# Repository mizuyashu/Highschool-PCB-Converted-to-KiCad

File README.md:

# Highschool-PCB-Converted-to-KiCad
the pcb that I made in the stem club workshop that was ordered on jlcpbc for free from the onboard hackclub free pcb thing hackclub was doing for highschoolers converted from the easy eda files to KiCad

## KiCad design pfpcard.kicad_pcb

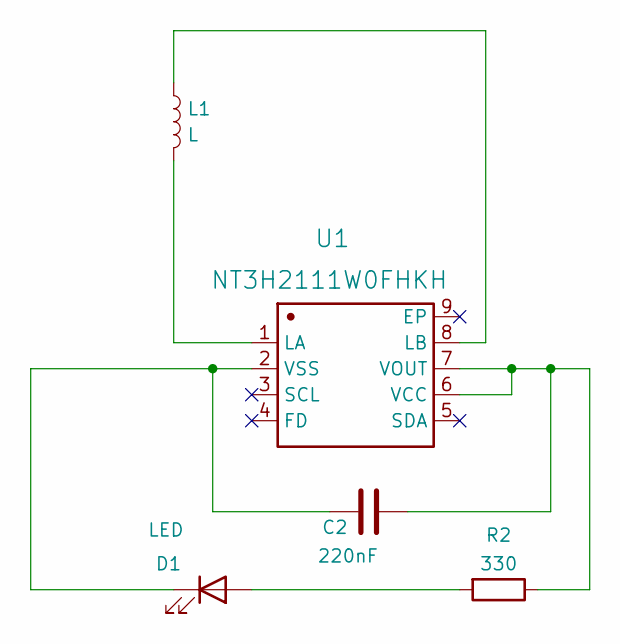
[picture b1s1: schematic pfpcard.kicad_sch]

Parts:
C2: 220nF; C_0603_1608Metric
D1: LED; LED_0805_2012Metric
L1: L; 25X48MM_NFC_ANTENNA
R2: 330; R_0603_1608Metric
U1: NT3H2111W0FHKH; XQFN-8_L1.6-W1.6-P0.50-BL; Manufacturer Part NT3H2111W0FHKH

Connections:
unnamed: D1.2 (A), R2.2
unnamed: C2.1, D1.1 (K), U1.2 (VSS)
unnamed: L1.2, U1.1 (LA)
unnamed: L1.1, U1.8 (LB)
unnamed: C2.2, R2.1, U1.6 (VCC), U1.7 (VOUT)

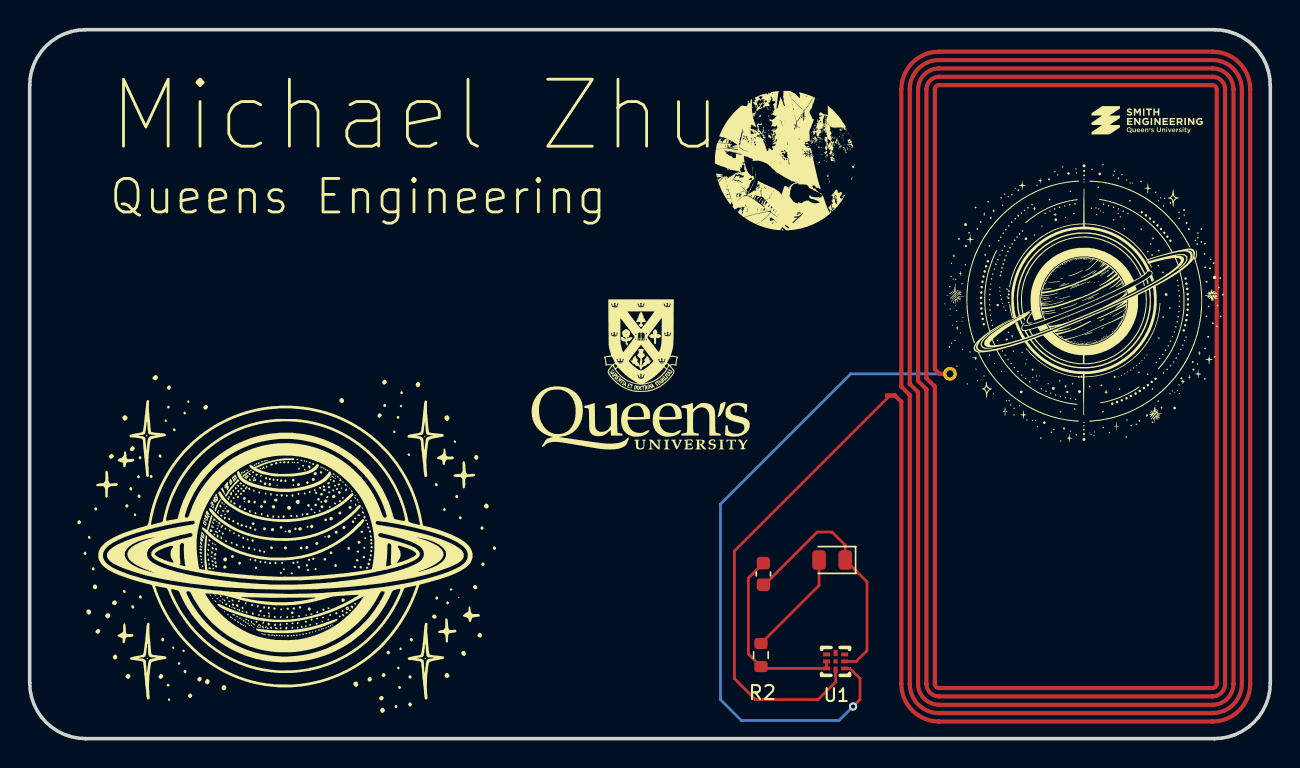
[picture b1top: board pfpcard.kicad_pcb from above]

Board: 2 copper layers, 88.9 x 50.8 mm, 5 parts (0 on the bottom side), 5 nets.

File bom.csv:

Designator,Footprint,Quantity,Value,LCSC Part #
C2,603,1,220nF,
D1,805,1,LED,
R2,603,1,330Ω,
U1,XQFN-8_L1.6-W1.6-P0.50-BL,1,NT3H2111W0FHKH,
